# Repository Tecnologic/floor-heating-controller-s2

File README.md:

# floor-heating-controller-s2
 with current controlled valve acutators

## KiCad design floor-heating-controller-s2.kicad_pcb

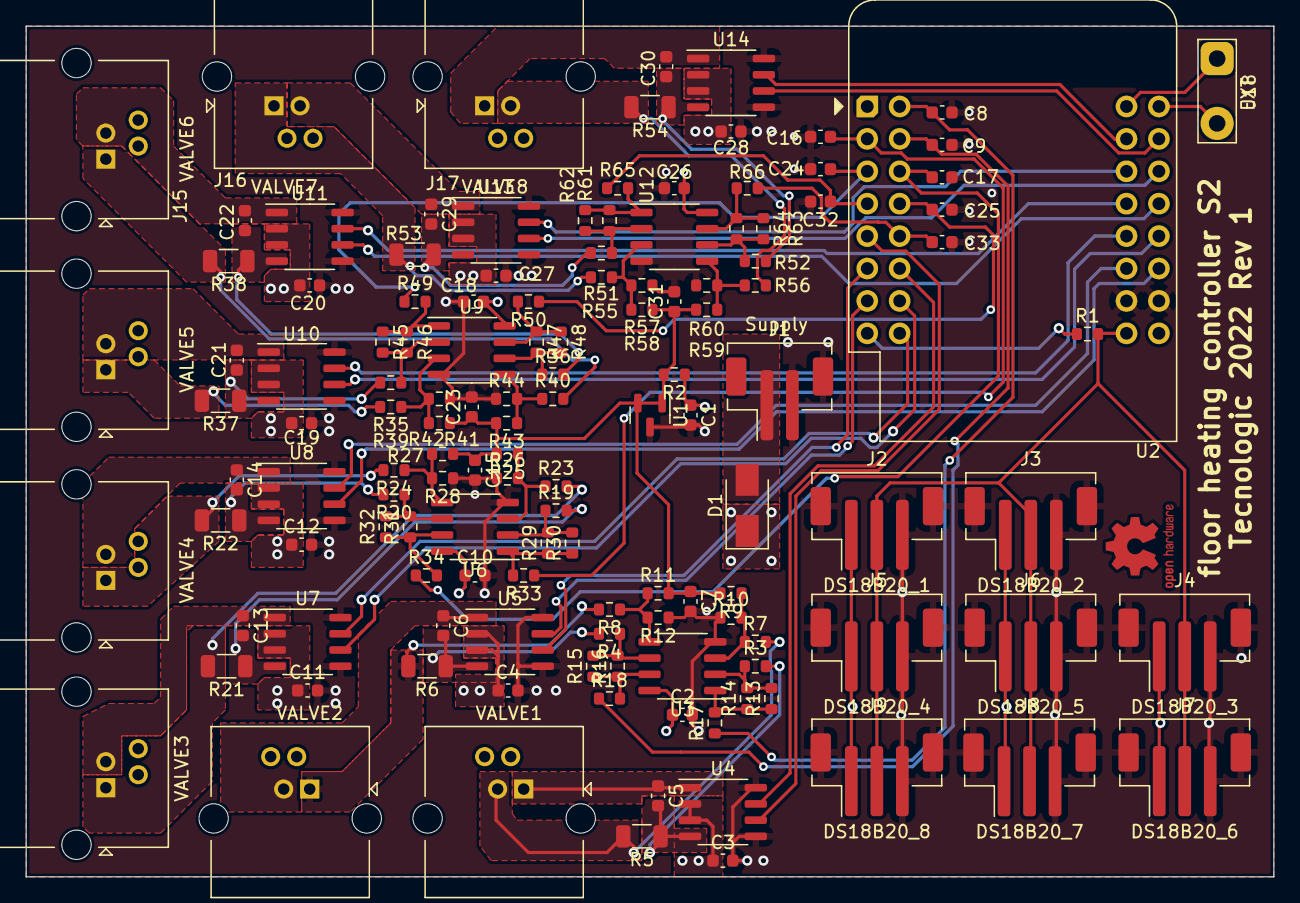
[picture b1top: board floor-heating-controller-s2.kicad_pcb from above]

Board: 4 copper layers, 97.8 x 66.7 mm, 132 parts (0 on the bottom side), 80 nets.

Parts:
C1, C2, C3, C4, C5, C6, C7, C10, C11, C12, C13, C14, C15, C18, C19, C20, C21, C22, C23, C26, C27, C28, C29, C30, C31: 100n; C_0603_1608Metric
C8, C9, C16, C17, C24, C25, C32, C33: 1n; C_0603_1608Metric
D1: SS54; D_SMA
J1: Supply; JST_PH_B2B-PH-SM4-TB_1x02-1MP_P2.00mm_Vertical
J2: DS18B20_1; JST_PH_B3B-PH-SM4-TB_1x03-1MP_P2.00mm_Vertical
J3: DS18B20_2; JST_PH_B3B-PH-SM4-TB_1x03-1MP_P2.00mm_Vertical
J4: DS18B20_3; JST_PH_B3B-PH-SM4-TB_1x03-1MP_P2.00mm_Vertical
J5: DS18B20_4; JST_PH_B3B-PH-SM4-TB_1x03-1MP_P2.00mm_Vertical
J6: DS18B20_5; JST_PH_B3B-PH-SM4-TB_1x03-1MP_P2.00mm_Vertical
J7: DS18B20_6; JST_PH_B3B-PH-SM4-TB_1x03-1MP_P2.00mm_Vertical
J8: DS18B20_7; JST_PH_B3B-PH-SM4-TB_1x03-1MP_P2.00mm_Vertical
J9: DS18B20_8; JST_PH_B3B-PH-SM4-TB_1x03-1MP_P2.00mm_Vertical
J10: VALVE1; RJ14_Connfly_DS1133-S4_Horizontal
J11: VALVE2; RJ14_Connfly_DS1133-S4_Horizontal
J12: VALVE3; RJ14_Connfly_DS1133-S4_Horizontal
J13: VALVE4; RJ14_Connfly_DS1133-S4_Horizontal
J14: VALVE5; RJ14_Connfly_DS1133-S4_Horizontal
J15: VALVE6; RJ14_Connfly_DS1133-S4_Horizontal
J16: VALVE7; RJ14_Connfly_DS1133-S4_Horizontal
J17: VALVE8; RJ14_Connfly_DS1133-S4_Horizontal
J18: EXT; TestPoint_2Pads_Pitch5.08mm_Drill1.3mm
R1: 1k; R_0603_1608Metric
R2, R3, R4, R7, R8, R17, R18, R19, R20, R23, R24, R33, R34, R35, R36, R39, R40, R49, R50, R51, R52, R55, R56, R65, R66: 330R; R_0603_1608Metric
R5, R6, R21, R22, R37, R38, R53, R54: 0R1; R_1206_3216Metric
R9, R10, R11, R12, R13, R14, R15, R16, R25, R26, R27, R28, R29, R30, R31, R32, R41, R42, R43, R44, R45, R46, R47, R48, R57, R58, R59, R60, R61, R62, R63, R64: 47k; R_0603_1608Metric
U1: CJ431; SOT-23
U2: WeMos_S2_mini; WEMOS_S2_mini
U3, U6, U9, U12: LM358; SO-8_3.9x4.9mm_P1.27mm
U4, U5, U7, U8, U10, U11, U13, U14: L9110S; SO-8_3.9x4.9mm_P1.27mm

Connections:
+2V5: C7.1, C15.1, C23.1, C31.1, R2.2, R9.2, R11.2, R25.2, R27.2, R41.2, R43.2, R57.2, R59.2, U1.1 (K), U1.2 (REF)
+3V3: C2.1, C10.1, C18.1, C26.1, R1.1, U2.8 (3V3), U3.8 (V+), U6.8 (V+), U9.8 (V+), U12.8 (V+)
+5V: C1.1, C3.1, C4.1, C11.1, C12.1, C19.1, C20.1, C27.1, C28.1, D1.1 (K), J2.1, J3.1, J4.1, J5.1, J6.1, J7.1, J8.1, J9.1, R2.1, U2.9 (VBUS), U4.2 (VCC), U4.3 (VCC), U5.2 (VCC), U5.3 (VCC), U7.2 (VCC), U7.3 (VCC), U8.2 (VCC), U8.3 (VCC), U10.2 (VCC), U10.3 (VCC), U11.2 (VCC), U11.3 (VCC), U13.2 (VCC), U13.3 (VCC), U14.2 (VCC), U14.3 (VCC)
/DS18B20: J2.2, J3.2, J4.2, J5.2, J6.2, J7.2, J8.2, J9.2, R1.2, U2.25 (GPIO15)
/motor_output_1/MOT1_A: C5.1, J10.1, U4.1 (OUT_A)
/motor_output_1/MOT1_B: J10.3, R5.2, R7.2
/motor_output_1/MOT2_A: C6.1, J11.3, U5.1 (OUT_A)
/motor_output_1/MOT2_B: J11.1, R6.2, R8.2
/motor_output_2/MOT1_A: C13.1, J12.3, U7.1 (OUT_A)
/motor_output_2/MOT1_B: J12.1, R21.2, R23.2
/motor_output_2/MOT2_A: C14.1, J13.3, U8.1 (OUT_A)
/motor_output_2/MOT2_B: J13.1, R22.2, R24.2
/motor_output_3/MOT1_A: C21.1, J14.3, U10.1 (OUT_A)
/motor_output_3/MOT1_B: J14.1, R37.2, R39.2
/motor_output_3/MOT2_A: C22.1, J15.3, U11.1 (OUT_A)
/motor_output_3/MOT2_B: J15.1, R38.2, R40.2
/motor_output_4/MOT1_A: C29.1, J16.3, U13.1 (OUT_A)
/motor_output_4/MOT1_B: J16.1, R53.2, R55.2
/motor_output_4/MOT2_A: C30.1, J17.1, U14.1 (OUT_A)
/motor_output_4/MOT2_B: J17.3, R54.2, R56.2
CUR1: C8.1, R17.1, U2.17 (GPIO1)
CUR2: C9.1, R18.1, U2.18 (GPIO2)
CUR3: C16.1, R33.1, U2.2 (GPIO3)
CUR4: C17.1, R34.1, U2.19 (GPIO4)
CUR5: C24.1, R49.1, U2.3 (GPIO5)
CUR6: C25.1, R50.1, U2.20 (GPIO6)
CUR7: C32.1, R65.1, U2.4 (GPIO7)
CUR8: C33.1, R66.1, U2.21 (GPIO8)
GND: C1.2, C2.2, C3.2, C4.2, C7.2, C8.2, C9.2, C10.2, C11.2, C12.2, C15.2, C16.2, C17.2, C18.2, C19.2, C20.2, C23.2, C24.2, C25.2, C26.2, C27.2, C28.2, C31.2, C32.2, C33.2, J1.2, J1.MP (MountPin), J2.3, J2.MP (MountPin), J3.3, J3.MP (MountPin), J4.3, J4.MP (MountPin), J5.3, J5.MP (MountPin), J6.3, J6.MP (MountPin), J7.3, J7.MP (MountPin), J8.3, J8.MP (MountPin), J9.3, J9.MP (MountPin), R10.1, R12.1, R26.1, R28.1, R42.1, R44.1, R58.1, R60.1, U1.3 (A), U2.10 (GND), U2.26 (GND), U3.4 (V-), U4.5 (GND), U4.8 (GND), U5.5 (GND), U5.8 (GND), U6.4 (V-), U7.5 (GND), U7.8 (GND), U8.5 (GND), U8.8 (GND), U9.4 (V-), U10.5 (GND), U10.8 (GND), U11.5 (GND), U11.8 (GND), U12.4 (V-), U13.5 (GND), U13.8 (GND), U14.5 (GND), U14.8 (GND)
IN1_A: U2.5 (GPIO9), U4.6 (IN_A)
IN1_B: U2.22 (GPIO10), U4.7 (IN_B)
IN2_A: U2.6 (GPIO11), U5.6 (IN_A)
IN2_B: U2.7 (GPIO12), U5.7 (IN_B)
IN3_A: U2.23 (GPIO13), U7.6 (IN_A)
IN3_B: U2.24 (GPIO14), U7.7 (IN_B)
IN4_A: U2.11 (GPIO16), U8.6 (IN_A)
IN4_B: U2.27 (GPIO17), U8.7 (IN_B)
IN5_A: U2.12 (GPIO18), U10.6 (IN_A)
IN5_B: U2.28 (GPIO21), U10.7 (IN_B)
IN6_A: U2.13 (GPIO33), U11.6 (IN_A)
IN6_B: U2.29 (GPIO34), U11.7 (IN_B)
IN7_A: U2.14 (GPIO35), U13.6 (IN_A)
IN7_B: U2.30 (GPIO36), U13.7 (IN_B)
IN8_A: U2.15 (GPIO37), U14.6 (IN_A)
IN8_B: U2.31 (GPIO38), U14.7 (IN_B)
unnamed: C5.2, R3.2, R5.1, U4.4 (OUT_B)
unnamed: C6.2, R4.2, R6.1, U5.4 (OUT_B)
unnamed: C13.2, R19.2, R21.1, U7.4 (OUT_B)
unnamed: C14.2, R20.2, R22.1, U8.4 (OUT_B)
unnamed: C21.2, R35.2, R37.1, U10.4 (OUT_B)
unnamed: C22.2, R36.2, R38.1, U11.4 (OUT_B)
unnamed: C29.2, R51.2, R53.1, U13.4 (OUT_B)
unnamed: C30.2, R52.2, R54.1, U14.4 (OUT_B)
unnamed: D1.2 (A), J1.1
unnamed: J18.1, U2.32 (GPIO40)
unnamed: J18.2, U2.16 (GPIO39)
unnamed: R7.1, R9.1, R10.2, U3.3 (+)
unnamed: R8.1, R11.1, R12.2, U3.5 (+)
unnamed: R13.1, R14.1, R17.2, U3.1
unnamed: R3.1, R13.2, R14.2, U3.2 (-)
unnamed: R15.1, R16.1, R18.2, U3.7
unnamed: R4.1, R15.2, R16.2, U3.6 (-)
unnamed: R19.1, R29.2, R30.2, U6.2 (-)
unnamed: R20.1, R31.2, R32.2, U6.6 (-)
unnamed: R23.1, R25.1, R26.2, U6.3 (+)
unnamed: R24.1, R27.1, R28.2, U6.5 (+)
unnamed: R29.1, R30.1, R33.2, U6.1
unnamed: R31.1, R32.1, R34.2, U6.7
unnamed: R35.1, R45.2, R46.2, U9.2 (-)
unnamed: R36.1, R47.2, R48.2, U9.6 (-)
unnamed: R39.1, R41.1, R42.2, U9.3 (+)
unnamed: R40.1, R43.1, R44.2, U9.5 (+)
unnamed: R45.1, R46.1, R49.2, U9.1
unnamed: R47.1, R48.1, R50.2, U9.7
unnamed: R51.1, R61.2, R62.2, U12.2 (-)
unnamed: R52.1, R63.2, R64.2, U12.6 (-)
unnamed: R55.1, R57.1, R58.2, U12.3 (+)
unnamed: R56.1, R59.1, R60.2, U12.5 (+)
unnamed: R61.1, R62.1, R65.2, U12.1
unnamed: R63.1, R64.1, R66.2, U12.7

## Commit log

2022-11-27 start of a current controlled valve
2022-11-28 changed gain of opamps
2022-11-29 finished schematics
2022-11-30 first placing
2022-12-02 First routing cycle nearly complete
2022-12-03 production ready
2022-12-08 ordered
2023-09-06 started costum component in esphome for motor control
2023-10-07 started custom component
2023-10-09 adc build but crashes
2023-10-10 got adc kinda working
2023-10-30 Esp Version and cdc log running
2023-10-31 started with 5.1.1 adc driver
2023-11-02 platformio arduino esp32 3.0 config
2023-11-03 first implemention
2023-11-04 implementing task
2023-11-14 added rtos notification
2023-11-15 added current calculation
2023-11-15 next fixes
2023-11-17 first successful build with bdc component
2023-11-17 running with adc and pwm. needs scope for further debug
2023-11-18 started littlefs webserver with wifi manager
2023-11-19 got wifi manager code needs to be cleaned
2023-11-22 need to use webserver impelentation without async lib
2023-11-24 use just stock libs
2023-11-24 just added ota code
2023-11-25 builds at least
2023-11-28 anoyed
2023-11-28 kinda works with stok web server
2023-11-30 hey builds with asynctcp server
2023-12-15 pretesting code snippets
2023-12-17 arduino is anoying, no return values just useless logs.
2023-12-17 espidf in pio is acuitally working better than esp ide
2023-12-17 motor runs but l9220s is not what i expected it to be
2023-12-18 added final board config to build for both boards
2023-12-19 fixed platformio.ini
2023-12-19 pwm is running, now figuring the analog part out.
2023-12-22 added adc readings
2023-12-22 print take to long
2023-12-22 updated git ignore
2023-12-22 rename the software root directory
2023-12-22 pio update
2023-12-23 updated pio
2023-12-24 changed pwm freq
2023-12-27 rededigned the hardware layer
2023-12-27 small build fix
2023-12-28 added model for speed and position
2023-12-29 added voltage output stuff for first test of the motor model
2023-12-29 small fix
2023-12-30 added pi controller
2023-12-30 current and voltage direction made simular
2024-01-04 started new arch with channel wise config
2024-01-05 save recources
2024-01-05 god way though the rework
2024-01-08 a little progress
2024-01-09 first running version after arch change
2024-01-12 found the issue with the hpoint on ledc
2024-01-12 pwm seams to work as "center aligned"
2024-01-16 more investigation on current measurement. current measurement is only unidirectional for now.
2024-01-16 Need to fix PWM Pins to defined states during opperation on other channel
2024-01-18 current control is running in both directions
